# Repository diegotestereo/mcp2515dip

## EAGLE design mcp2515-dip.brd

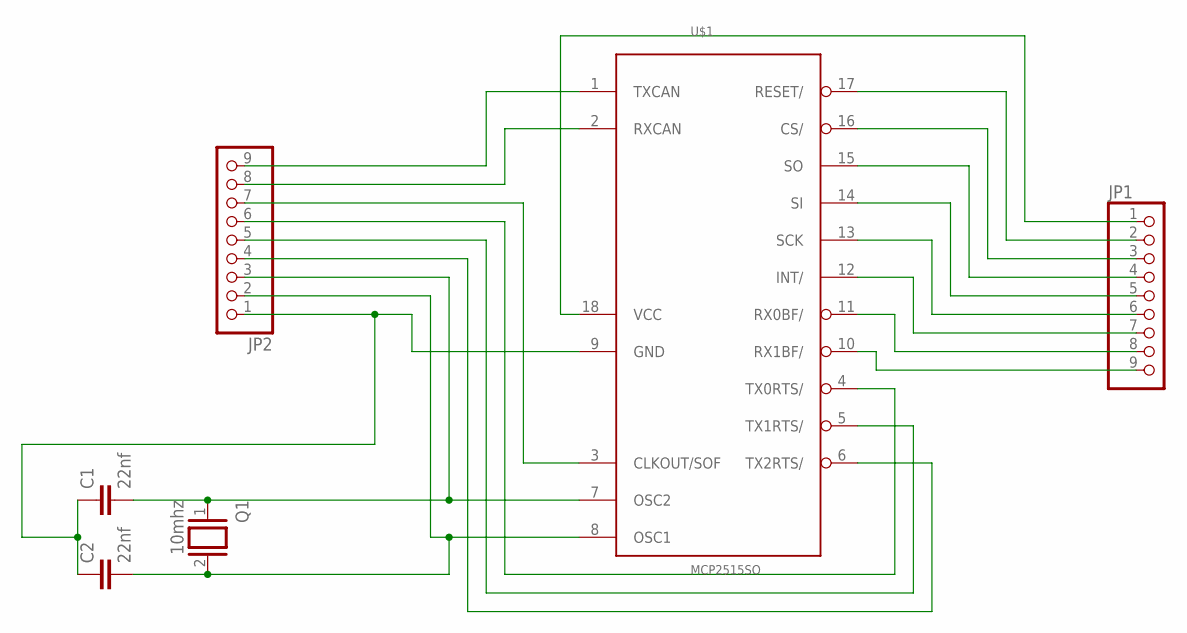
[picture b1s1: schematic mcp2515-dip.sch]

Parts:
C1, C2: 22nf; C050-035X075
JP1, JP2: PINHD-1X9; 1X09
Q1: 10mhz; QS
U$1: MCP2515SO; SO18L

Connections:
GND: C1.1, C2.1, JP2.1, U$1.9 (GND)
unnamed: JP2.9, U$1.1 (TXCAN)
unnamed: JP2.8, U$1.2 (RXCAN)
unnamed: JP2.7, U$1.3 (CLKOUT/SOF)
unnamed: JP2.6, U$1.4 (TX0RTS/)
unnamed: JP2.5, U$1.5 (TX1RTS/)
unnamed: JP2.4, U$1.6 (TX2RTS/)
unnamed: C1.2, JP2.3, Q1.1, U$1.7 (OSC2)
unnamed: JP1.9, U$1.10 (RX1BF/)
unnamed: JP1.8, U$1.11 (RX0BF/)
unnamed: JP1.7, U$1.12 (INT/)
unnamed: JP1.6, U$1.13 (SCK)
unnamed: JP1.5, U$1.14 (SI)
unnamed: JP1.4, U$1.15 (SO)
unnamed: JP1.3, U$1.16 (CS/)
unnamed: JP1.2, U$1.17 (RESET/)
unnamed: JP1.1, U$1.18 (VCC)
unnamed: C2.2, JP2.2, Q1.2, U$1.8 (OSC1)

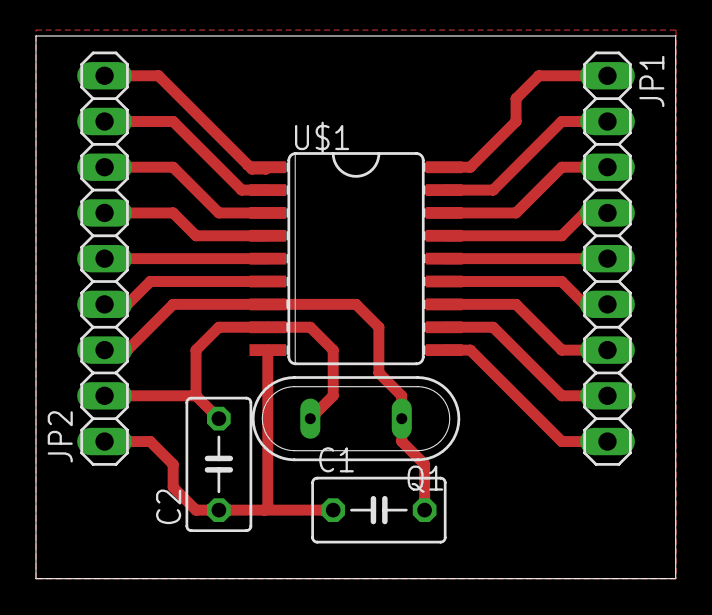
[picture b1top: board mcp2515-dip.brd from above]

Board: 2 copper layers, 35.5 x 30.1 mm, 6 parts (0 on the bottom side), 18 nets.

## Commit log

2016-02-23 :lollipop: Added .gitattributes & .gitignore files
